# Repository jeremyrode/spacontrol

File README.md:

# spacontrol
IoT Work for my Caldera Vacanza Hot Tub

## General Info
I have a Caldera Vacanza Hot Tub in my house and I love it, with one exception: it heats on demand.  With electric time of use (TOU) rates, I can save money if the hot tub would heat during off-peak rates.  Goal is to reverse engineer the protocol used to signal button presses.  Phase 1 is to have a cron script adjust the setpoints so that the heating occurs during off-peak hours.  Phase 2 (current) is to use Google Calendar to schedule the virtual button presses to follow the complex TOU schedule.  Phase 3 (In progress) is to reverse engineer the status screen protocol, and forward the status to a website.  This has been stymied by the complex bit banging that is going on between these systems.  The patterns seem to change, see Keypad Commands section.

## Status

Phase 2 is working well for a year now, it pulls the desired temprature from a [Google Calendar via the API](/googlecalendardaemon), then schedules them.  I thought this was clever, so [I broke out this code as an example](https://github.com/jeremyrode/CalendarScraper) and it made [HACAKADAY!](https://hackaday.com/2022/10/25/using-google-calendar-for-machines-to-keep-track-of-human-days/)

## Quickstart

Easiest way is to have a cron job running tools/temp_up.js and tools/temp_down.js at the appropriate times for cheap TOU power.

Add the following to the crontab:
```
08 0 * * * /home/pi/spacontrol/tools/temp_down.js
10 0 * * * /home/pi/spacontrol/tools/temp_up.js
50 5 * * * /home/pi/spacontrol/tools/temp_down.js
```
Here at 12:08 AM the temp is turned down to ensure a start from 80 deg, as this code is "open-loop".  At 12:10 AM the temp is turned up to 103, then at 5:50AM the temp is turned back down to 80 deg.  Ideally the spa will be at ~100 deg in the evening when I'm ready to go in.

## Detailed Status
I have successfully reverse engineered the button press protocol.  Playing the protocol back proved to be tricky, as the keypad seems to be polled, so even when no buttons are pressed, the keypad reports status every ~40ms.  Injecting commands on top of the polled screen traffic does not result in the controller registering a button press. I suspect there is a switch "debouncing" algorithm that only registers a press if button polls several times in a row.  This necessitated a more complicated hardware design, where a GPIO on the raspberry pi is used to switch a mux, muting the traffic from the screen while virtual button presses are generated.

## Screen status 
77 degrees
Mostly
4a962bf252fefefa6600
I saw one:
4a962be452fefefa6600
80 degrees
4a962bf252fefefa6600

## Keypad Commands

The keypad seems to report status every ~40ms back to the controller.  I believe it is polled based off of commands sent to the pad, as the traffic seems to halt if the controller->keypad serial line is disconnected.  Baud rate is 115200, with 2-stop bits, but this doesn't seem to matter.

| Button  | Code (Hex) |
| :------:        |:----:|
| Idle            | 584D5300036b00000166 |
| Unknown / Idle  | 584D5300014b0144 |
| Jets            | 584D5300036b00100176 |
| Temp Down       | 584D5300036b0008016e |
| Temp Up         | 584D5300036b00020168 |
| Lights          | 584D5300036b00200186 |

Some how this has changed???

Now I'm seeing at idle (captured with serial_test.py):

58534d00010000f958534d00031a00830198

58534d00031a00830198

58534d00031a00830198

58534d00031a00830198

58534d00010000f958534d00031a00830198

58534d00031a00830198

No idea!, but the old commands seem to work on the sending side!

Seems to persist.  Is the the raspberryPi or the mainboard?

Putting this on hold, quite frankly it doesn't matter, the old commands above still work.

## Hardware details

This is the connector we would like to inject commands into:

Probing with an oscilloscope revealed the following pinout:

| Pin #  | Function |
| :------:|:----:|
| 1 | Screen->Controller (RS-422) |
| 2 | +12V |
| 3 | Controller->Screen (RS-422) |
| 4 | GND |
| 5 | Controller->Screen (RS-422) |
| 6 | Screen->Controller (RS-422) |

I have purposely not marked the RS-422 polarity, as I want to double check.  The PCB has jumpers that toggle the MAX3089's polarity inputs, so the PCB as designed will work with either polarity.

My first hand-built prototype.  

This is basically a break-out board, with a 12V to 5V converter for convenience so that I don't have to use an extension cord with a USB power supply to power the Pi Zero.  I used the [sparkfun RS485 shield](https://www.sparkfun.com/products/retired/13706) I had laying around from my [last reverse engineering project](https://github.com/jeremyrode/elancontrol).

This prototype successfully captured screen codes, and could play the codes back, but as its RS-422 transmitter is in parallel with the screens transmitter code playback never worked.  I suspect that because of the polled nature of the system transmitting status every 40ms, that when a button press code is injected some sort of button debouncing algorithm rejects the single button press code.  At this point I bit the bullet and I designed a raspberry Pi Zero "hat" PCB (see the PCB directory) that uses a MAX14778 MUX to inject commands (using a MAX3089 to translate the Pi's serial port to the spa's RS-422), defaulting to a passthrough mode where the normal screen traffic is unaffected, selected via GPIO5.  I also threw in a 12V to 5V regulator to power the raspberry Pi from the 12V screen supply.  Watch out the Vacanza controller will power cycle this 12V if valid commands are not returned for a couple of seconds or so!  That threw my debugging through a loop!

Trusty Macrofab (I highly recommend!) fabricated it no problem:

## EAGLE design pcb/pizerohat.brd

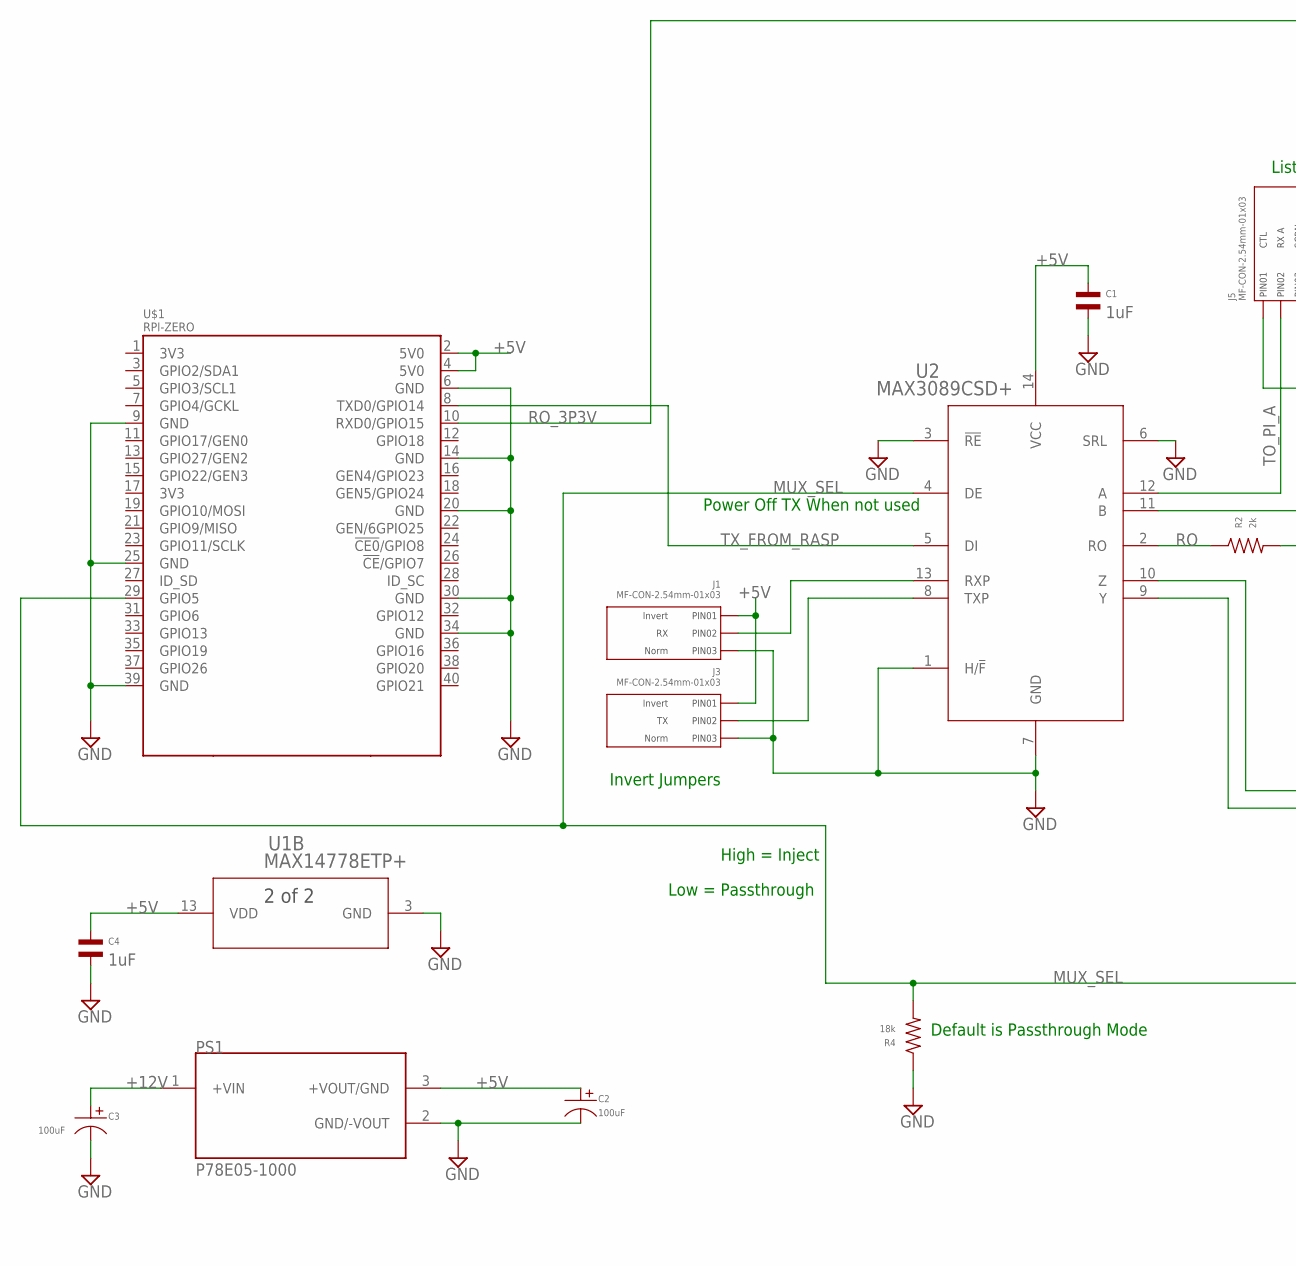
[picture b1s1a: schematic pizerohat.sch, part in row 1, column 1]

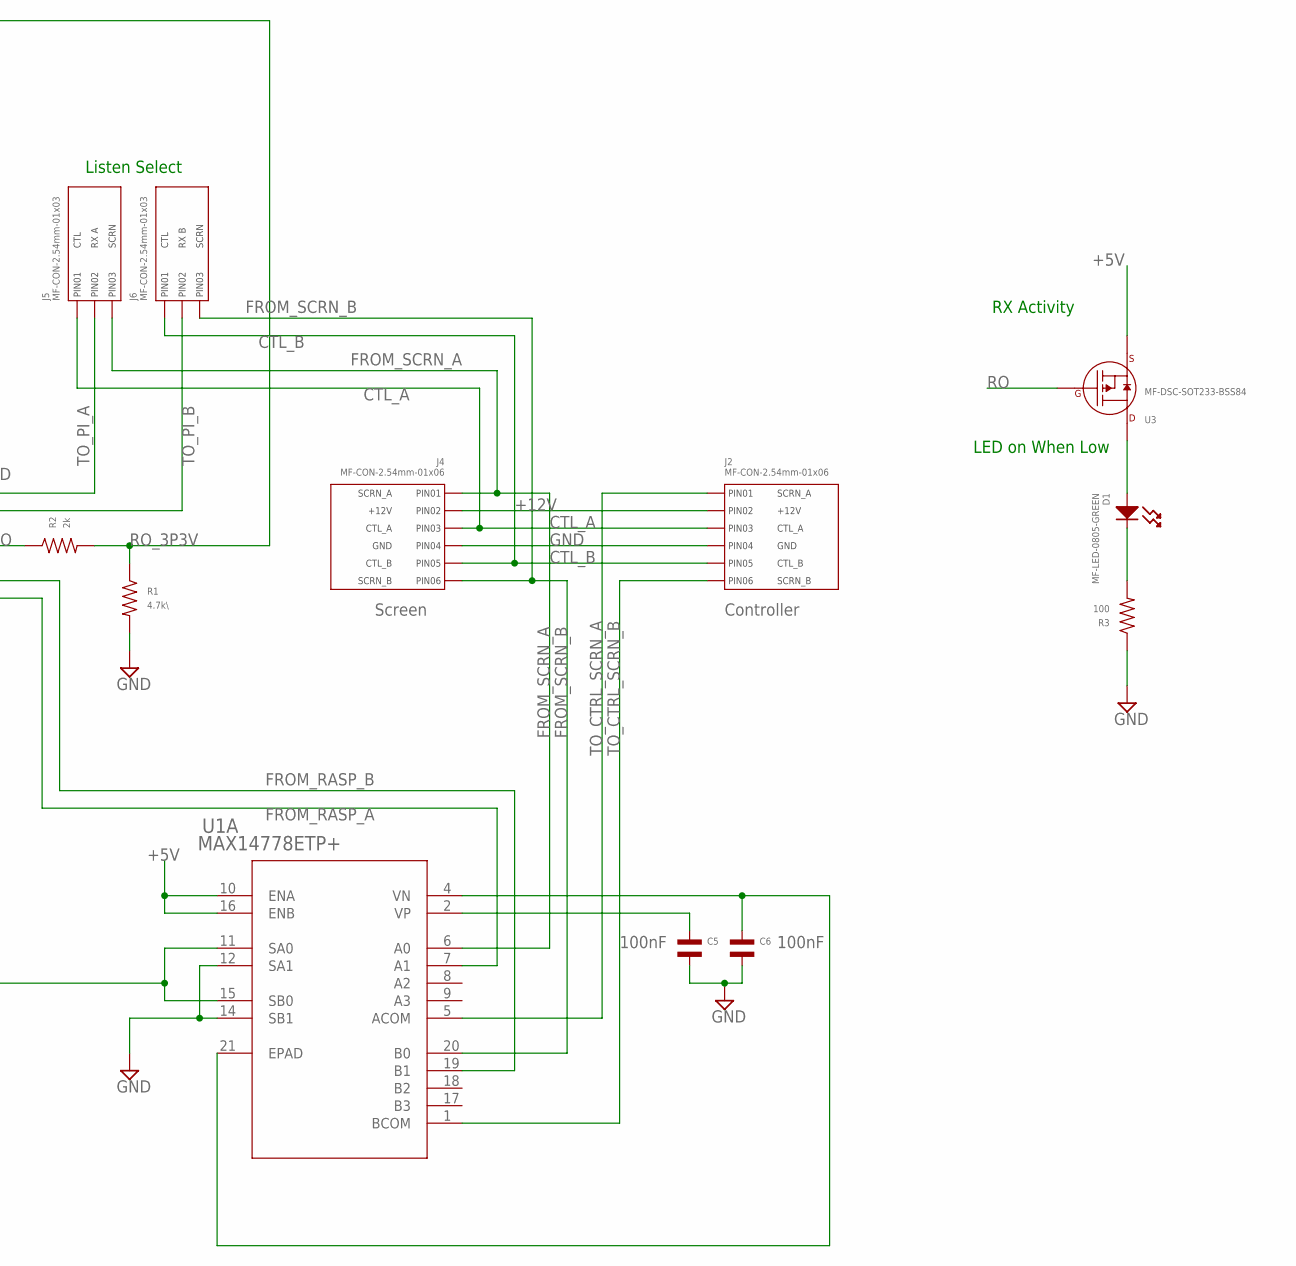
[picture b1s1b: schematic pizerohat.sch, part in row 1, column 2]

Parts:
C1, C4: CAPACITOR_NP_0603; C0603; MPN MF-CAP-0603-1uF
C2, C3: 100uF; CP6.3MM; MPN MF-CAP-6.3MM-100uF
C5, C6: CAPACITOR_NP_0805; C0805; MPN MF-CAP-0805-0.1uF
D1: MF-LED-0805-GREEN; LED0805
J1, J3, J5, J6: MF-CON-2.54mm-01x03; PTH_2.54MM_01X03
J2, J4: MF-CON-2.54mm-01x06; PTH_2.54MM_01X06
PS1: P78E05-1000; CONV_P78E05-1000; MPN P78E05-1000
R1: 4.7k\; R0603; MPN MF-RES-0603-4.7K
R2: 2k; R0603; MPN MF-RES-0603-2K
R3: 100; R0603; MPN MF-RES-0603-100
R4: 18k; R0603; MPN MF-RES-0603-18K
U1: MAX14778ETP+; 21-0140L_T2055-4; MPN MAX14778ETP+
U2: MAX3089CSD+; 21-0041B_14; MPN MAX3089CSD+
U3: MF-DSC-SOT233-BSS84; SOT-23-3
U$1: RPI-ZERO; RASPBERRYPI_BASTELSTUBE_V13_RASPI_BOARD_B+_FULL

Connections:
+5V: C1.P$1, C2.P$1, C4.P$1, J1.P$1 (PIN1), J3.P$1 (PIN1), PS1.3 (+VOUT/GND), U1.10 (ENA), U1.13 (VDD), U1.16 (ENB), U2.14 (VCC), U3.P$2 (SOURCE), U$1.2 (5V0), U$1.4 (5V0)
+12V: C3.P$1, J2.P$2 (PIN2), J4.P$2 (PIN2), PS1.1 (+VIN)
CTL_A: J2.P$3 (PIN3), J4.P$3 (PIN3), J5.P$1 (PIN1)
CTL_B: J2.P$5 (PIN5), J4.P$5 (PIN5), J6.P$1 (PIN1)
FROM_RASP_A: U1.7 (A1), U2.9 (Y)
FROM_RASP_B: U1.19 (B1), U2.10 (Z)
FROM_SCRN_A: J4.P$1 (PIN1), J5.P$3 (PIN3), U1.6 (A0)
FROM_SCRN_B: J4.P$6 (PIN6), J6.P$3 (PIN3), U1.20 (B0)
GND: C1.P$2, C2.P$2, C3.P$2, C4.P$2, C5.P$2, C6.P$2, J1.P$3 (PIN3), J2.P$4 (PIN4), J3.P$3 (PIN3), J4.P$4 (PIN4), PS1.2 (GND/-VOUT), R1.P$2, R3.P$1, R4.P$1, U1.3 (GND), U1.12 (SA1), U1.14 (SB1), U2.1 (H/!F), U2.3 (!RE), U2.6 (SRL), U2.7 (GND), U$1.6 (GND), U$1.9 (GND), U$1.14 (GND), U$1.20 (GND), U$1.25 (GND), U$1.30 (GND), U$1.34 (GND), U$1.39 (GND)
MUX_SEL: R4.P$2, U1.11 (SA0), U1.15 (SB0), U2.4 (DE), U$1.29 (GPIO5)
unnamed: J1.P$2 (PIN2), U2.13 (RXP)
unnamed: J3.P$2 (PIN2), U2.8 (TXP)
unnamed: C6.P$1, U1.4 (VN), U1.21 (EPAD)
unnamed: D1.CATHODE, R3.P$2
unnamed: C5.P$1, U1.2 (VP)
unnamed: D1.ANODE, U3.P$3 (DRAIN)
RO: R2.P$1, U2.2 (RO), U3.P$1 (GATE)
RO_3P3V: R1.P$1, R2.P$2, U$1.10 (RXD0/GPIO15)
TO_CTRL_SCRN_A: J2.P$1 (PIN1), U1.5 (ACOM)
TO_CTRL_SCRN_B: J2.P$6 (PIN6), U1.1 (BCOM)
TO_PI_A: J5.P$2 (PIN2), U2.12 (A)
TO_PI_B: J6.P$2 (PIN2), U2.11 (B)
TX_FROM_RASP: U2.5 (DI), U$1.8 (TXD0/GPIO14)

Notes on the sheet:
Default is Passthrough Mode
RX Activity
LED on When Low
Invert Jumpers
Listen Select
High = Inject
Low = Passthrough
Power Off TX When not used

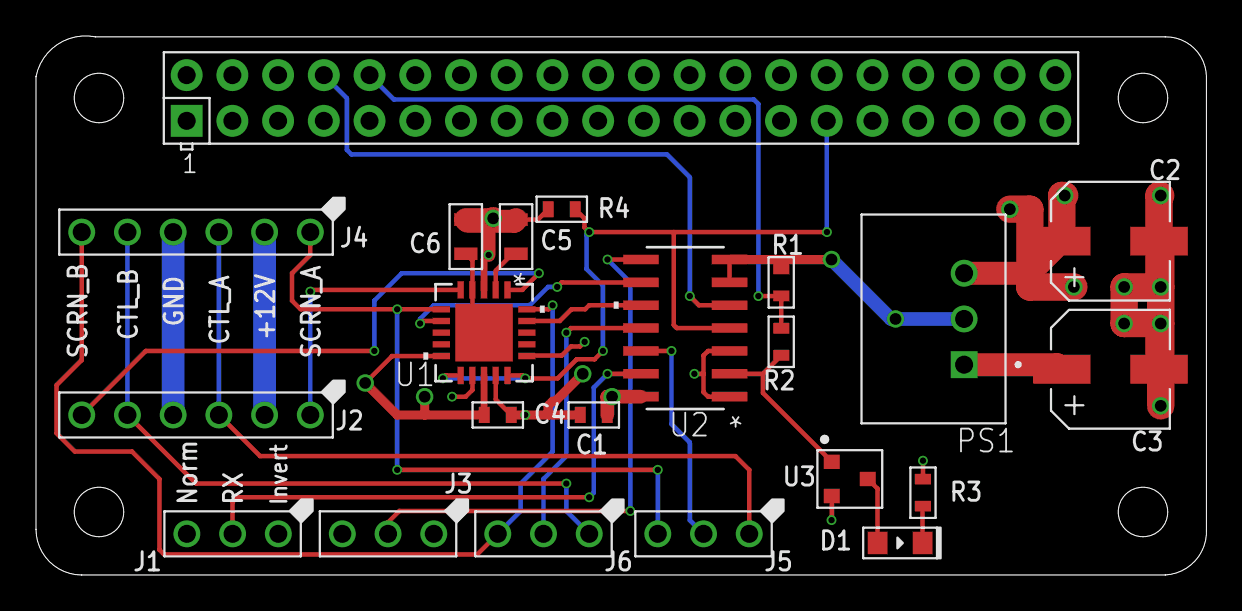
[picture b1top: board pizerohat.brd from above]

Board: 4 copper layers, 65.0 x 29.9 mm, 22 parts (0 on the bottom side), 23 nets.

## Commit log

2019-11-24 Inital Tool Checkin
2019-11-26 pcb inital checkin
2019-11-30 PCB Update
2019-11-30 Rordered mux pins, added pulldown for default muxsel
2019-12-01 Power TX down when not in use
2020-01-16 Working with new PCBgit status
2020-01-16 Inital testing and frontend work
2020-01-17 Temp up and down working!
2020-01-17 Updated docs
2020-01-17 Final tweaks to temp up/down utils
2020-01-17 Documentation
2020-01-17 more documentation
2020-01-17 typo
2020-03-09 Debug insane serial changes
2020-03-09 document new serial behaviour
2020-03-09 consoldated readme
2020-12-22 Seasonal temp adjustment and trying to figure out new patterns
2020-12-24 New SSH key test
2021-08-05 temp update
2021-09-22 Initial Google Calendar API
2021-09-22 Repeated API pulls working
2021-09-24 Inital Testing with Log File
2021-09-24 Spa command sending integrated, short term tested
2021-09-24 Last min tweaks before long testing
2021-09-24 Final tweaks for long term testing
2021-09-24 Long term testing
2021-09-25 Tweaked logging during testing
2021-09-25 Passed live testing
2021-09-30 Cleaned up Auth, had errors afeter 5 days
2021-10-05 testing cleanup
2021-10-06 Added mutex for plan
2021-10-08 document refresh token expiry problem
2021-10-14 Adapting tools for screen to CPU commands
2021-10-18 go strict, use null for obj delete
2021-10-18 minor cleanup
2021-10-25 add retry for API
2021-10-26 API error tweaking
2021-11-18 about to add reliability for overnight heats
2021-11-18 add reliability for overnight heats
2022-10-13 Migrate to Google API Key
2026-04-12 Gemini Fixes
2026-04-12 local changes on Pi
